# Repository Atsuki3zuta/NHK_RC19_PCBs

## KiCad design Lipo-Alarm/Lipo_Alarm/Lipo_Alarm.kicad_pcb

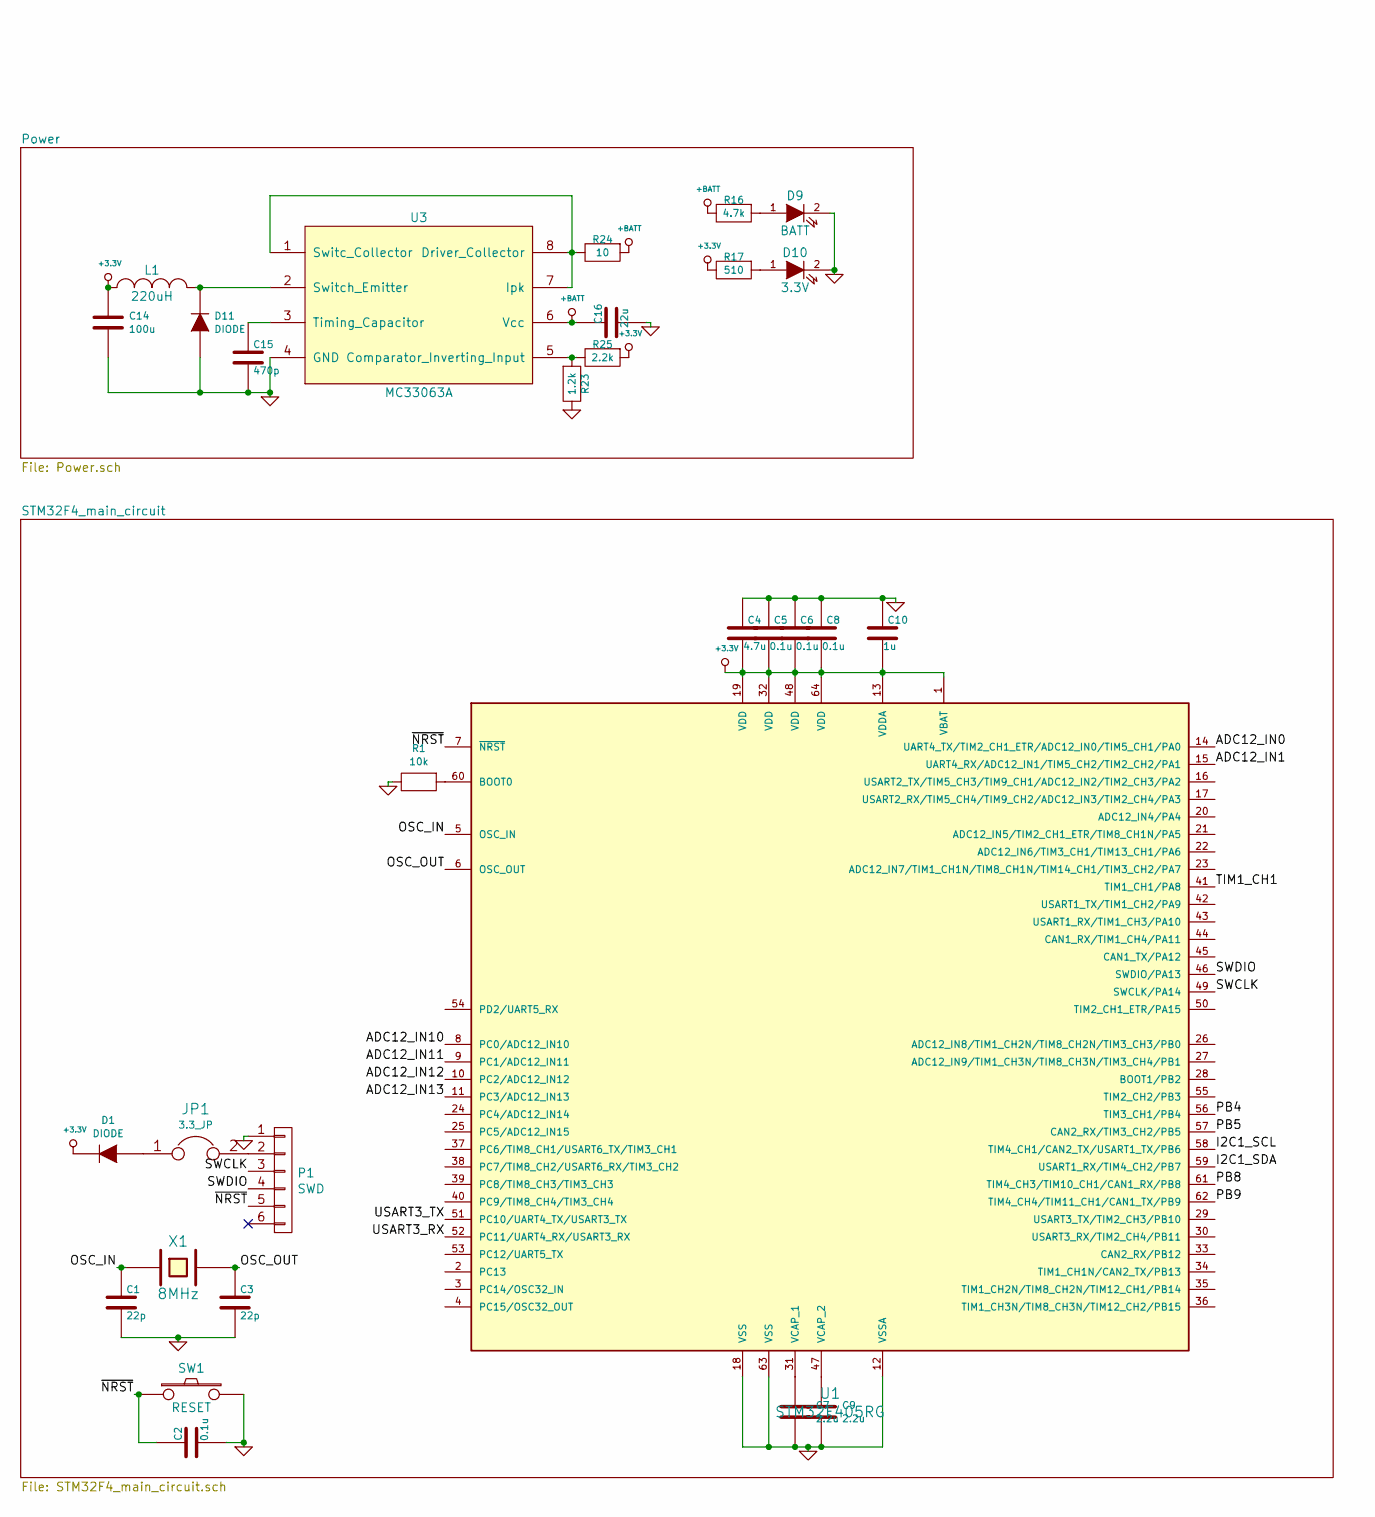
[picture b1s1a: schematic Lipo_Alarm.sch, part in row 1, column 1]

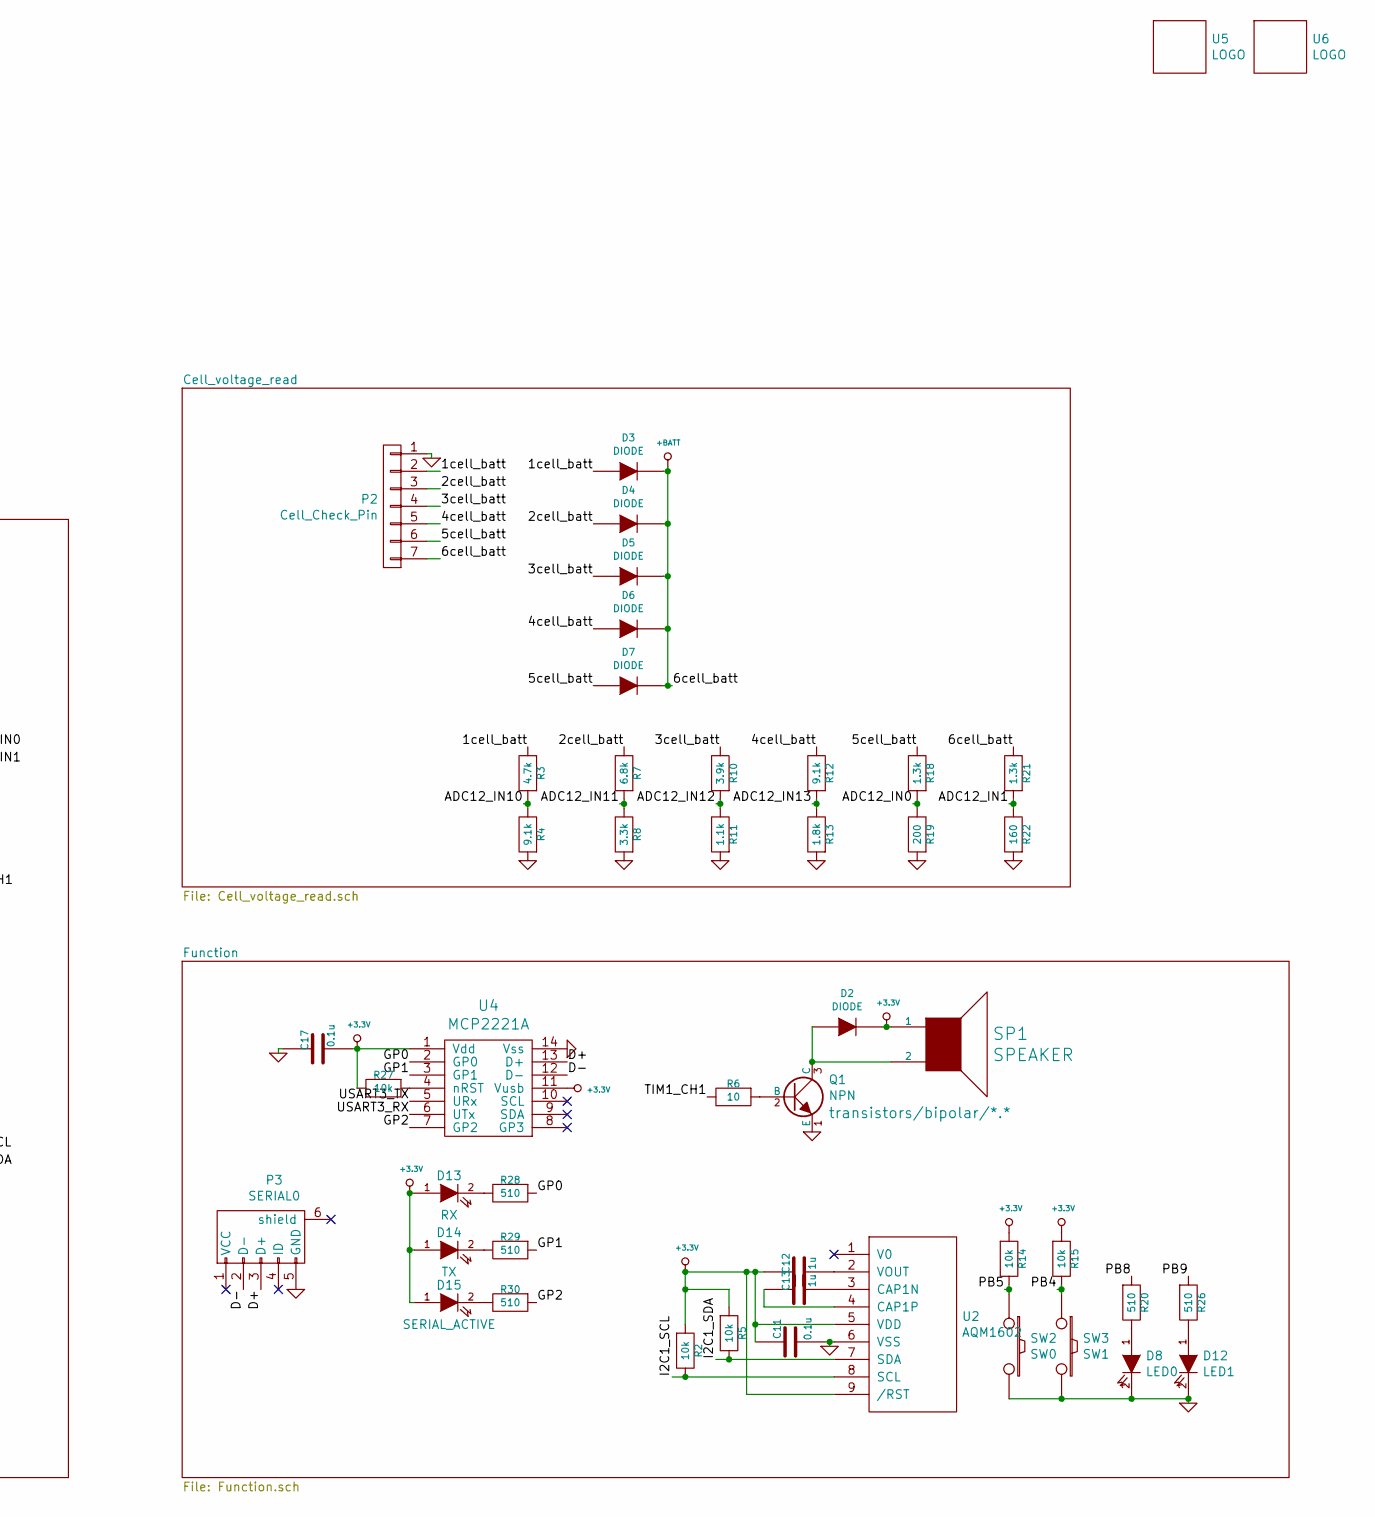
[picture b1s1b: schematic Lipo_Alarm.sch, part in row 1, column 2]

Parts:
C1, C3: 22p; C_0603
C2, C5, C6, C8, C11: 0.1u; C_0603
C4: 4.7u; C_0603
C7, C9: 2.2u; C_0603
C10, C12, C13: 1u; C_0603
C14: 100u; C_1206
C15: 470p; C_0603
C16: 22u; C_0805
C17: 0.1u; C_0805
D1, D2, D3, D4, D5, D6, D7, D11: DIODE; SOD-123
D8: LED0; LED_0603
D9: BATT; LED_0603
D10: 3.3V; LED_0603
D12: LED1; LED_0603
D13: RX; LED_0603
D14: TX; LED_0603
D15: SERIAL_ACTIVE; LED_0603
JP1: 3.3_JP; GS2
L1: 220uH; Inductor_Taiyo-Yuden_NR-60xx_HandSoldering
P1: SWD; ZH_6T
P2: Cell_Check_Pin; Pin_Header_Angled_1x07
P3: SERIAL0; USB_Micro-B_Molex_47346-0001
Q1: NPN; SOT-123
R1, R2, R5, R14, R15, R27: 10k; R_0603
R3, R16: 4.7k; R_0603
R4, R12: 9.1k; R_0603
R6, R24: 10; R_0603
R7: 6.8k; R_0603
R8: 3.3k; R_0603
R10: 3.9k; R_0603
R11: 1.1k; R_0603
R13: 1.8k; R_0603
R17, R20, R26, R28, R29, R30: 510; R_0603
R18, R21: 1.3k; R_0603
R19: 200; R_0603
R22: 160; R_0603
R23: 1.2k; R_0603
R25: 2.2k; R_0603
SP1: SPEAKER; UGCT7525AN4
SW1: RESET; SW_SPST_CK_RS282G05A3
SW2: SW0; SW_SPST_CK_RS282G05A3
SW3: SW1; SW_SPST_CK_RS282G05A3
U1: STM32F405RG; LQFP-64_10x10mm_Pitch0.5mm
U2: AQM1602
U3: MC33063A; SOIC-8_3.9x4.9mm_Pitch1.27mm
U4: MCP2221A; SOIC-14_3.9x8.7mm_Pitch1.27mm
U5: LOGO; Mini_Monster
U6: LOGO; Battery_logo_7.0x7.0
X1: 8MHz; Crystal_SMD_5032_2Pads

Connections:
+3.3V: C4.2, C5.2, C6.2, C8.2, C10.2, C11.2, C12.2, C14.1, C17.1, D1.1 (K), D2.1 (K), D13.1 (A), D14.1 (A), D15.1 (A), L1.1, R2.1, R5.1, R14.1, R15.1, R17.2, R25.1, R27.2, SP1.1, U1.1 (VBAT), U1.13 (VDDA), U1.19 (VDD), U1.32 (VDD), U1.48 (VDD), U1.64 (VDD), U2.5 (VDD), U2.9 (/RST), U4.1 (Vdd), U4.11 (Vusb)
+BATT: C16.2, D3.1 (K), D4.1 (K), D5.1 (K), D6.1 (K), D7.1 (K), P2.7, R16.2, R21.2, R24.1, U3.6 (Vcc)
/1cell_batt: D3.2 (A), P2.2, R3.2
/2cell_batt: D4.2 (A), P2.3, R7.2
/3cell_batt: D5.2 (A), P2.4, R10.2
/4cell_batt: D6.2 (A), P2.5, R12.2
/5cell_batt: D7.2 (A), P2.6, R18.2
/ADC12_IN0: R18.1, R19.2, U1.14 (UART4_TX/TIM2_CH1_ETR/ADC12_IN0/TIM5_CH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)
/ADC12_IN1: R21.1, R22.2, U1.15 (UART4_RX/ADC12_IN1/TIM5_CH2/TIM2_CH2/PA1)
/ADC12_IN10: R3.1, R4.2, U1.8 (PC0/ADC12_IN10)
/ADC12_IN11: R7.1, R8.2, U1.9 (PC1/ADC12_IN11)
/ADC12_IN12: R10.1, R11.2, U1.10 (PC2/ADC12_IN12)
/ADC12_IN13: R12.1, R13.2, U1.11 (PC3/ADC12_IN13)
/D+: P3.3 (D+), U4.13 (D+)
/D-: P3.2 (D-), U4.12 (D-)
/GP0: R28.1, U4.2 (GP0)
/GP1: R29.1, U4.3 (GP1)
/GP2: R30.1, U4.7 (GP2)
/I2C1_SCL: R2.2, U1.58 (TIM4_CH1/CAN2_TX/USART1_TX/PB6), U2.8 (SCL)
/I2C1_SDA: R5.2, U1.59 (USART1_RX/TIM4_CH2/PB7), U2.7 (SDA)
/OSC_IN: C1.1, U1.5 (OSC_IN), X1.1
/OSC_OUT: C3.1, U1.6 (OSC_OUT), X1.2
/PB4: R15.2, SW3.1, U1.56 (TIM3_CH1/PB4)
/PB5: R14.2, SW2.1, U1.57 (CAN2_RX/TIM3_CH2/PB5)
/PB8: R20.1, U1.61 (TIM4_CH3/TIM10_CH1/CAN1_RX/PB8)
/PB9: R26.1, U1.62 (TIM4_CH4/TIM11_CH1/CAN1_TX/PB9)
/SWCLK: P1.3, U1.49 (SWCLK/PA14)
/SWDIO: P1.4, U1.46 (SWDIO/PA13)
/TIM1_CH1: R6.2, U1.41 (TIM1_CH1/PA8)
/USART3_RX: U1.52 (PC11/UART4_RX/USART3_RX), U4.6 (UTx)
/USART3_TX: U1.51 (PC10/UART4_TX/USART3_TX), U4.5 (URx)
/~NRST: C2.2, P1.5, SW1.1, U1.7 (~NRST)
GND: C1.2, C2.1, C3.2, C4.1, C5.1, C6.1, C7.2, C8.1, C9.2, C10.1, C11.1, C14.2, C15.1, C16.1, C17.2, D8.2 (K), D9.2 (K), D10.2 (K), D11.2 (A), D12.2 (K), P1.1, P2.1, P3.5 (GND), Q1.1 (E), R1.2, R4.1, R8.1, R11.1, R13.1, R19.1, R22.1, R23.2, SW1.2, SW2.2, SW3.2, U1.12 (VSSA), U1.18 (VSS), U1.63 (VSS), U2.6 (VSS), U3.4 (GND), U4.14 (Vss)
unnamed: C7.1, U1.31 (VCAP_1)
unnamed: C9.1, U1.47 (VCAP_2)
unnamed: C12.1, U2.2 (VOUT)
unnamed: C13.1, U2.3 (CAP1N)
unnamed: C13.2, U2.4 (CAP1P)
unnamed: C15.2, U3.3 (Timing_Capacitor)
unnamed: D1.2 (A), JP1.1
unnamed: D2.2 (A), Q1.3 (C), SP1.2
unnamed: D8.1 (A), R20.2
unnamed: D9.1 (A), R16.1
unnamed: D10.1 (A), R17.1
unnamed: D11.1 (K), L1.2, U3.2 (Switch_Emitter)
unnamed: D12.1 (A), R26.2
unnamed: D13.2 (K), R28.2
unnamed: D14.2 (K), R29.2
unnamed: D15.2 (K), R30.2
unnamed: JP1.2, P1.2
unnamed: Q1.2 (B), R6.1
unnamed: R1.1, U1.60 (BOOT0)
unnamed: R23.1, R25.2, U3.5 (Comparator_Inverting_Input)
unnamed: R24.2, U3.1 (Switc_Collector), U3.7 (Ipk), U3.8 (Driver_Collector)
unnamed: R27.1, U4.4 (nRST)

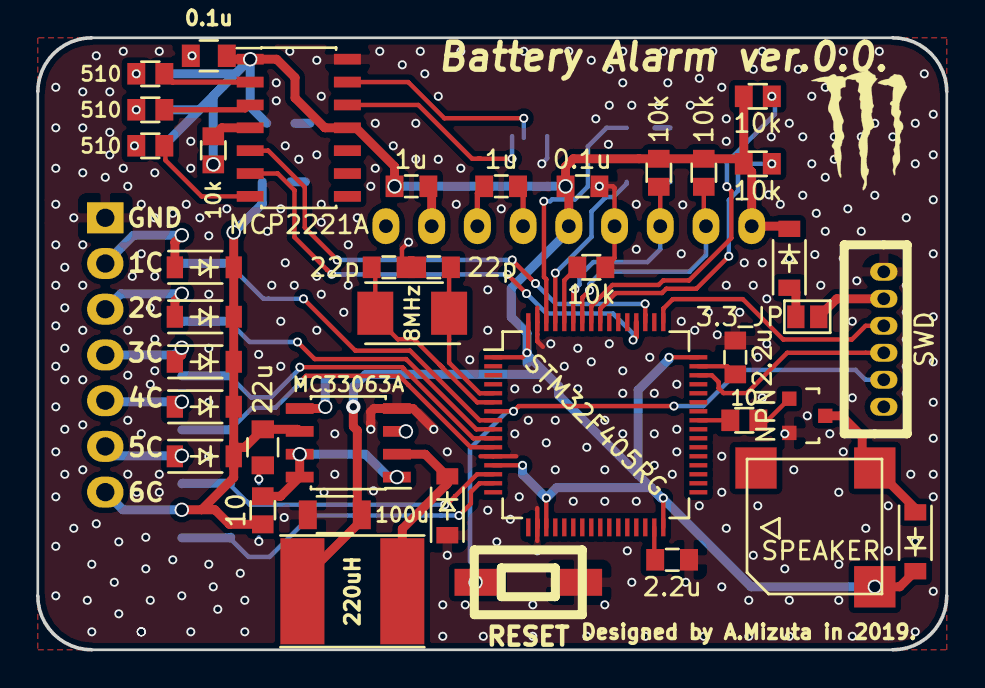
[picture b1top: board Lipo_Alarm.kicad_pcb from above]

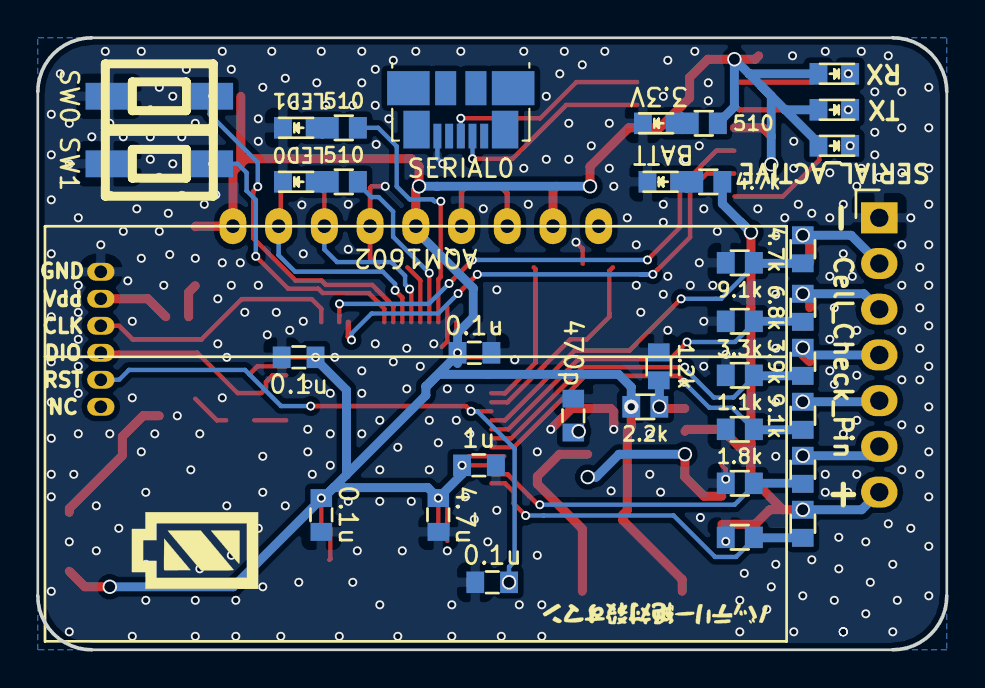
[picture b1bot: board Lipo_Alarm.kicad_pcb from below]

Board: 2 copper layers, 50.5 x 34.0 mm, 78 parts (38 on the bottom side), 55 nets.

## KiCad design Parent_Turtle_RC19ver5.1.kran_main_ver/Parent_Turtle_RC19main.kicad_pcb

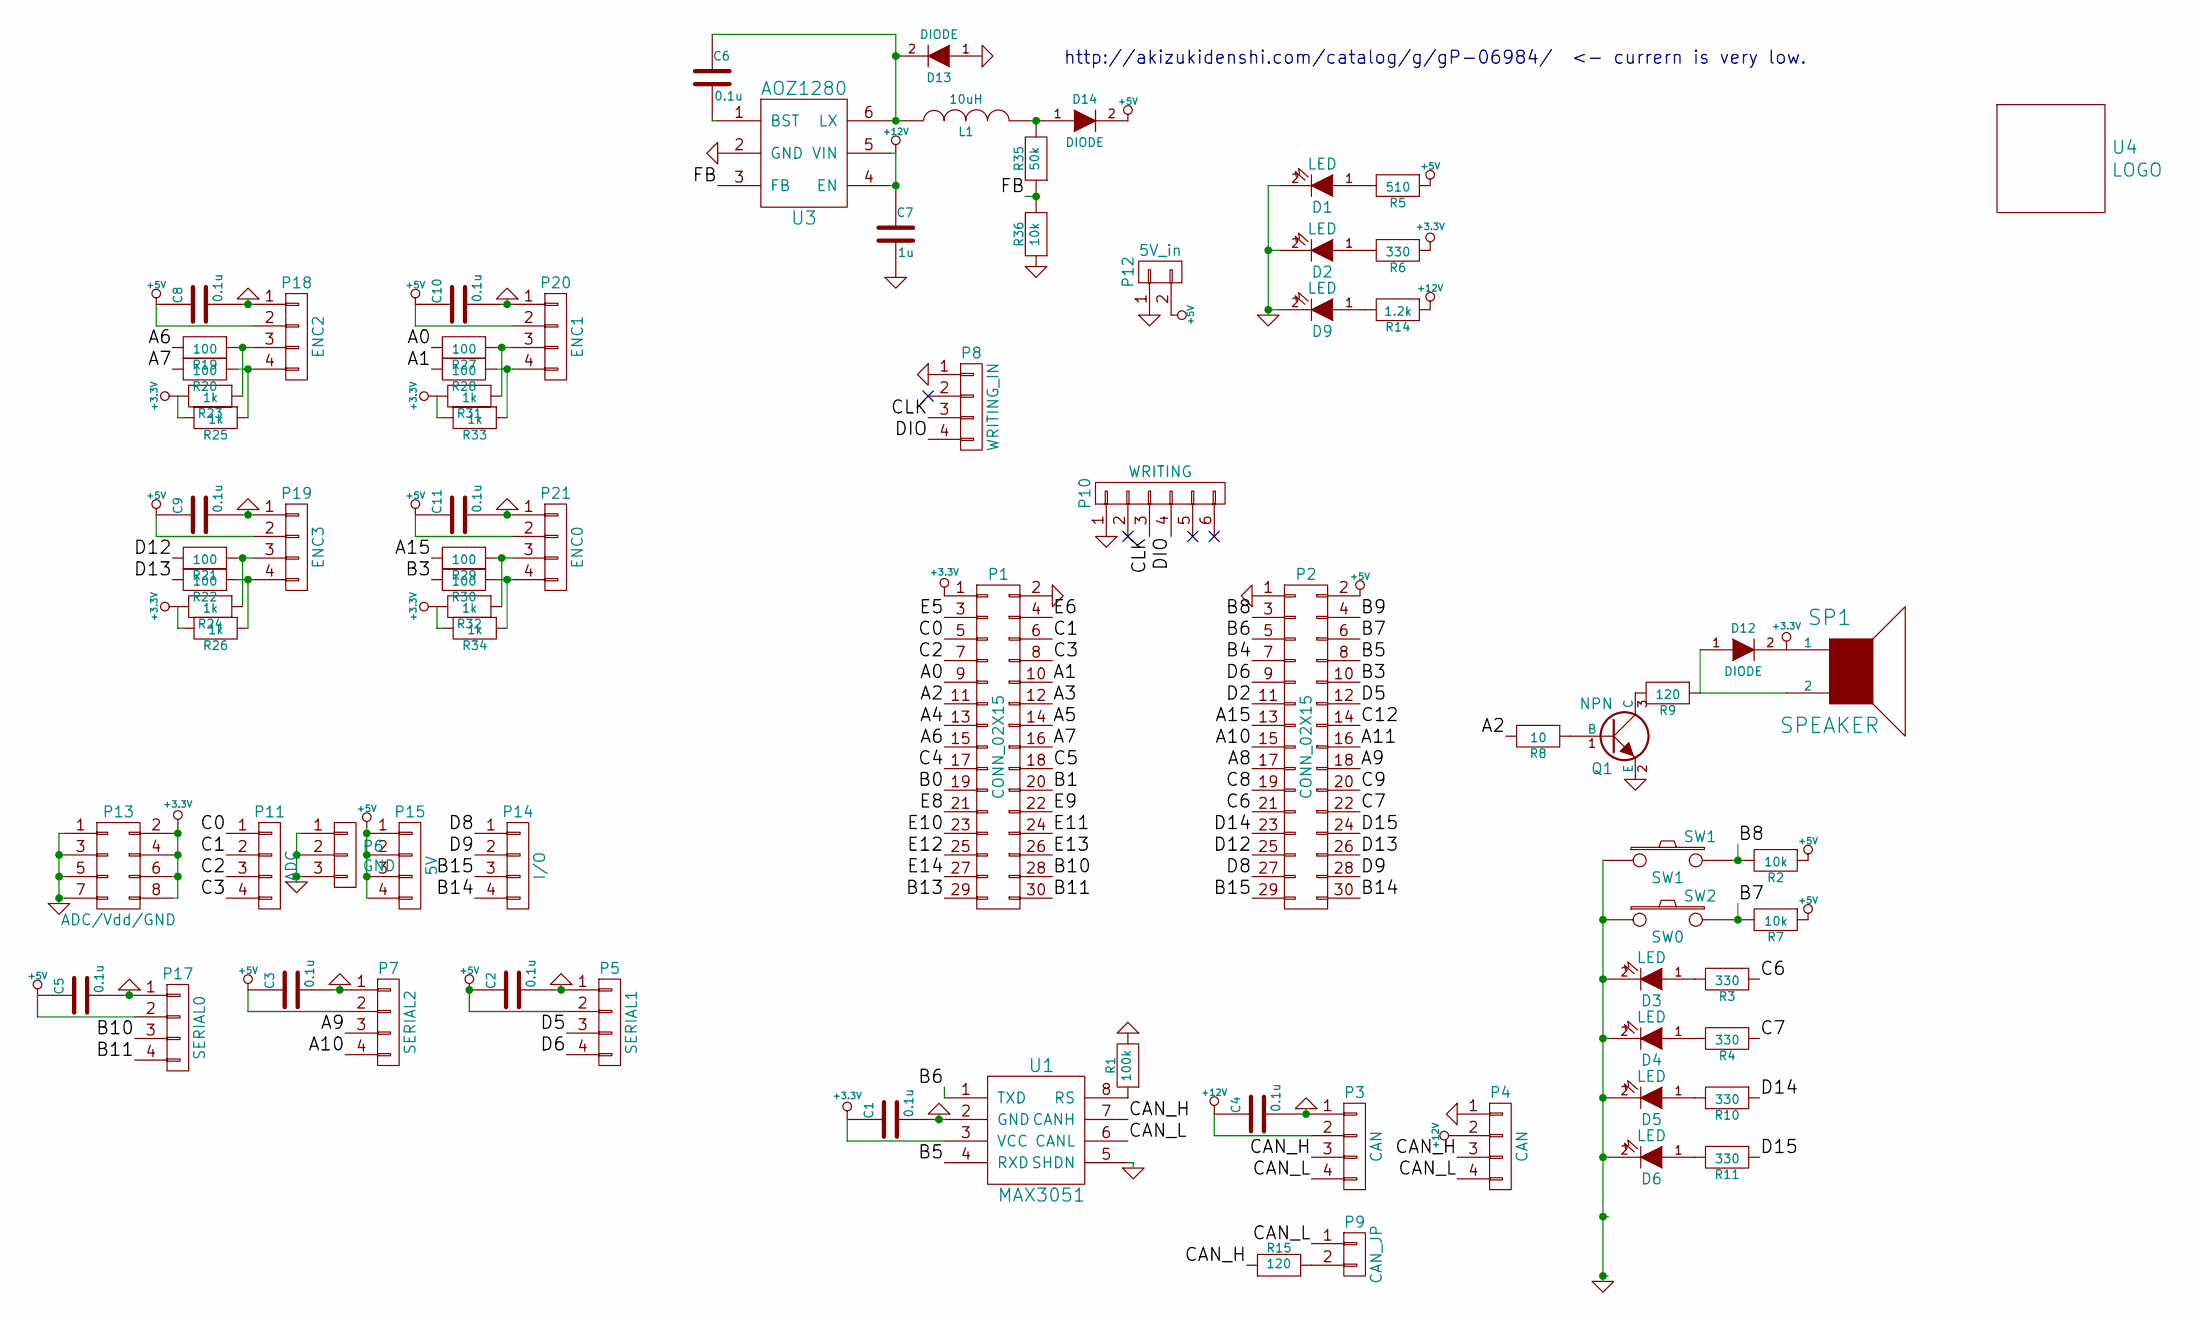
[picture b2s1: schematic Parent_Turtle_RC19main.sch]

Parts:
C1, C2, C3, C4, C5, C6, C8, C9, C10, C11: 0.1u; C_0603
C7: 1u; C_0603
D1, D2, D3, D4, D5, D6, D9: LED; LED-3MM
D12, D13, D14: DIODE; SOD-123
L1: 10uH; Inductor_Taiyo-Yuden_NR-50xx_HandSoldering
P1, P2: CONN_02X15; Socket_Strip_Straight_2x15
P3: CAN; XA_4T
P4: CAN; XA_4LC
P5: SERIAL1; XA_4T
P6: GND; PinHeader_1x03_P2.54mm_Vertical
P7: SERIAL2; XA_4T
P8: WRITING_IN; XA_4LC
P9: CAN_JP; Pin_Header_Straight_1x02
P10: WRITING; Socket_Strip_Straight_1x06
P11: ADC; Pin_Header_Straight_1x04
P12: 5V_in; XA_2T
P13: ADC/Vdd/GND; Pin_Header_Straight_2x04
P14: I/O; Pin_Header_Straight_1x04
P15: 5V; PinHeader_1x04_P2.54mm_Vertical
P17: SERIAL0; XA_4T
P18: ENC2; XA_4T
P19: ENC3; XA_4T
P20: ENC1; XA_4T
P21: ENC0; XA_4T
Q1: NPN; SOT-23
R1: 100k; R_0603
R2, R7, R36: 10k; R_0603
R3, R4, R6, R10, R11: 330; R_0603
R5: 510; R_0603
R8: 10; R_0603
R9, R15: 120; R_0603
R14: 1.2k; R_0603
R19, R20, R21, R22, R27, R28, R29, R30: 100; R_0603
R23, R24, R25, R26, R31, R32, R33, R34: 1k; R_0603
R35: 50k; R_0603
SP1: SPEAKER; UGCT7525AN4
SW1: SW1; RP_TroughHole_Button
SW2: SW0; RP_TroughHole_Button
U1: MAX3051; SOIC-8_3.9x4.9mm_Pitch1.27mm
U3: AOZ1280; TSOT-6-MK06A
U4: LOGO; Turtle_Logo_15.0x15.0

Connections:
+3.3V: C1.1, D12.2 (K), P1.1, P13.2, P13.4, P13.6, P13.8, R6.1, R23.2, R24.2, R25.2, R26.2, R31.2, R32.2, R33.2, R34.2, SP1.1, U1.3 (VCC)
+5V: C2.1, C3.1, C5.1, C8.1, C9.1, C10.1, C11.1, D14.2 (K), P2.2, P5.2, P7.2, P12.2, P15.1, P15.2, P15.3, P15.4, P17.2, P18.2, P19.2, P20.2, P21.2, R2.1, R5.1, R7.1
+12V: C4.1, C7.1, P3.2, P4.2, R14.1, U3.4 (EN), U3.5 (VIN)
/A0: P1.9, R27.2
/A1: P1.10, R28.2
/A2: P1.11, R8.2
/A3: P1.12
/A4: P1.13
/A5: P1.14
/A6: P1.15, R19.2
/A7: P1.16, R20.2
/A8: P2.17
/A9: P2.18, P7.3
/A10: P2.15, P7.4
/A11: P2.16
/A15: P2.13, R29.2
/B0: P1.19
/B1: P1.20
/B3: P2.10, R30.2
/B4: P2.7
/B5: P2.8, U1.4 (RXD)
/B6: P2.5, U1.1 (TXD)
/B7: P2.6, R7.2, SW2.2
/B8: P2.3, R2.2, SW1.2
/B9: P2.4
/B10: P1.28, P17.3
/B11: P1.30, P17.4
/B13: P1.29
/B14: P2.30, P14.4
/B15: P2.29, P14.3
/C0: P1.5, P11.1
/C1: P1.6, P11.2
/C2: P1.7, P11.3
/C3: P1.8, P11.4
/C4: P1.17
/C5: P1.18
/C6: P2.21, R3.1
/C7: P2.22, R4.1
/C8: P2.19
/C9: P2.20
/C12: P2.14
/CAN_H: P3.3, P4.3, R15.1, U1.7 (CANH)
/CAN_L: P3.4, P4.4, P9.1, U1.6 (CANL)
/CLK: P8.3, P10.3
/D2: P2.11
/D5: P2.12, P5.3
/D6: P2.9, P5.4
/D8: P2.27, P14.1
/D9: P2.28, P14.2
/D12: P2.25, R21.2
/D13: P2.26, R22.2
/D14: P2.23, R10.1
/D15: P2.24, R11.1
/DIO: P8.4, P10.4
/E5: P1.3
/E6: P1.4
/E8: P1.21
/E9: P1.22
/E10: P1.23
/E11: P1.24
/E12: P1.25
/E13: P1.26
/E14: P1.27
/FB: R35.1, R36.2, U3.3 (FB)
GND: C1.2, C2.2, C3.2, C4.2, C5.2, C7.2, C8.2, C9.2, C10.2, C11.2, D1.2 (K), D2.2 (K), D3.2 (K), D4.2 (K), D5.2 (K), D6.2 (K), D9.2 (K), D13.1 (A), P1.2, P2.1, P3.1, P4.1, P5.1, P6.1, P6.2, P6.3, P7.1, P8.1, P10.1, P12.1, P13.1, P13.3, P13.5, P13.7, P17.1, P18.1, P19.1, P20.1, P21.1, Q1.2 (E), R1.2, R36.1, SW1.1, SW2.1, U1.2 (GND), U1.5 (SHDN), U3.2 (GND)
unnamed: C6.1, D13.2 (K), L1.1, U3.6 (LX)
unnamed: C6.2, U3.1 (BST)
unnamed: D1.1 (A), R5.2
unnamed: D2.1 (A), R6.2
unnamed: D3.1 (A), R3.2
unnamed: D4.1 (A), R4.2
unnamed: D5.1 (A), R10.2
unnamed: D6.1 (A), R11.2
unnamed: D9.1 (A), R14.2
unnamed: D12.1 (A), R9.1, SP1.2
unnamed: D14.1 (A), L1.2, R35.2
unnamed: P9.2, R15.2
unnamed: P18.3, R19.1, R23.1
unnamed: P18.4, R20.1, R25.1
unnamed: P19.3, R21.1, R24.1
unnamed: P19.4, R22.1, R26.1
unnamed: P20.3, R27.1, R31.1
unnamed: P20.4, R28.1, R33.1
unnamed: P21.3, R29.1, R32.1
unnamed: P21.4, R30.1, R34.1
unnamed: Q1.1 (B), R8.1
unnamed: Q1.3 (C), R9.2
unnamed: R1.1, U1.8 (RS)

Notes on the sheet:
http://akizukidenshi.com/catalog/g/gP-06984/
<- currern is very low.

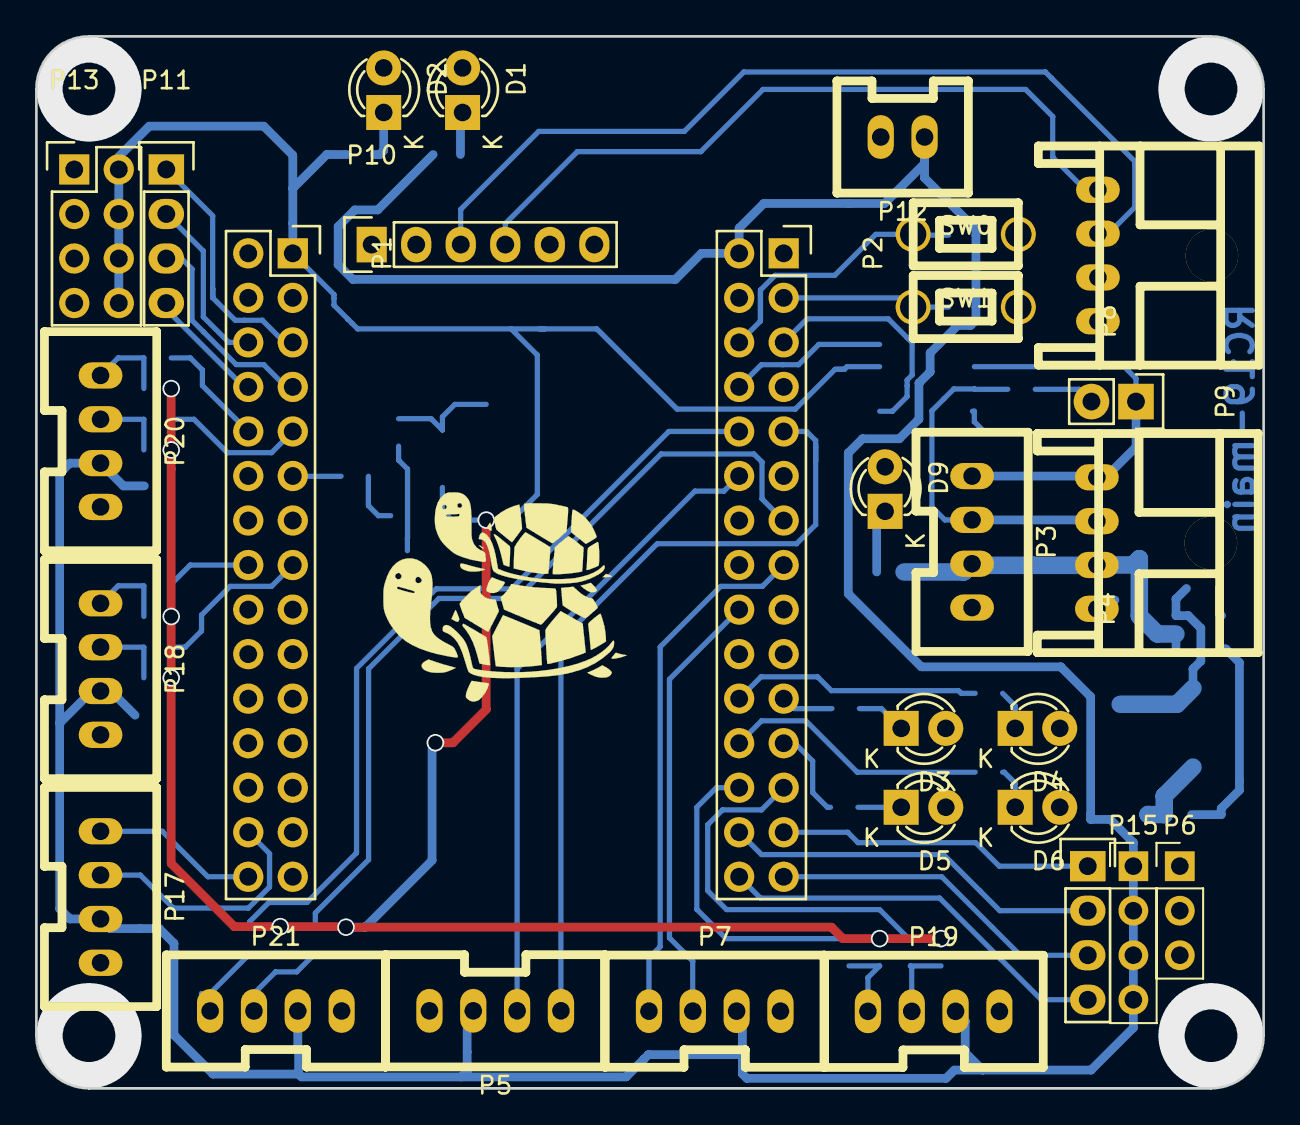
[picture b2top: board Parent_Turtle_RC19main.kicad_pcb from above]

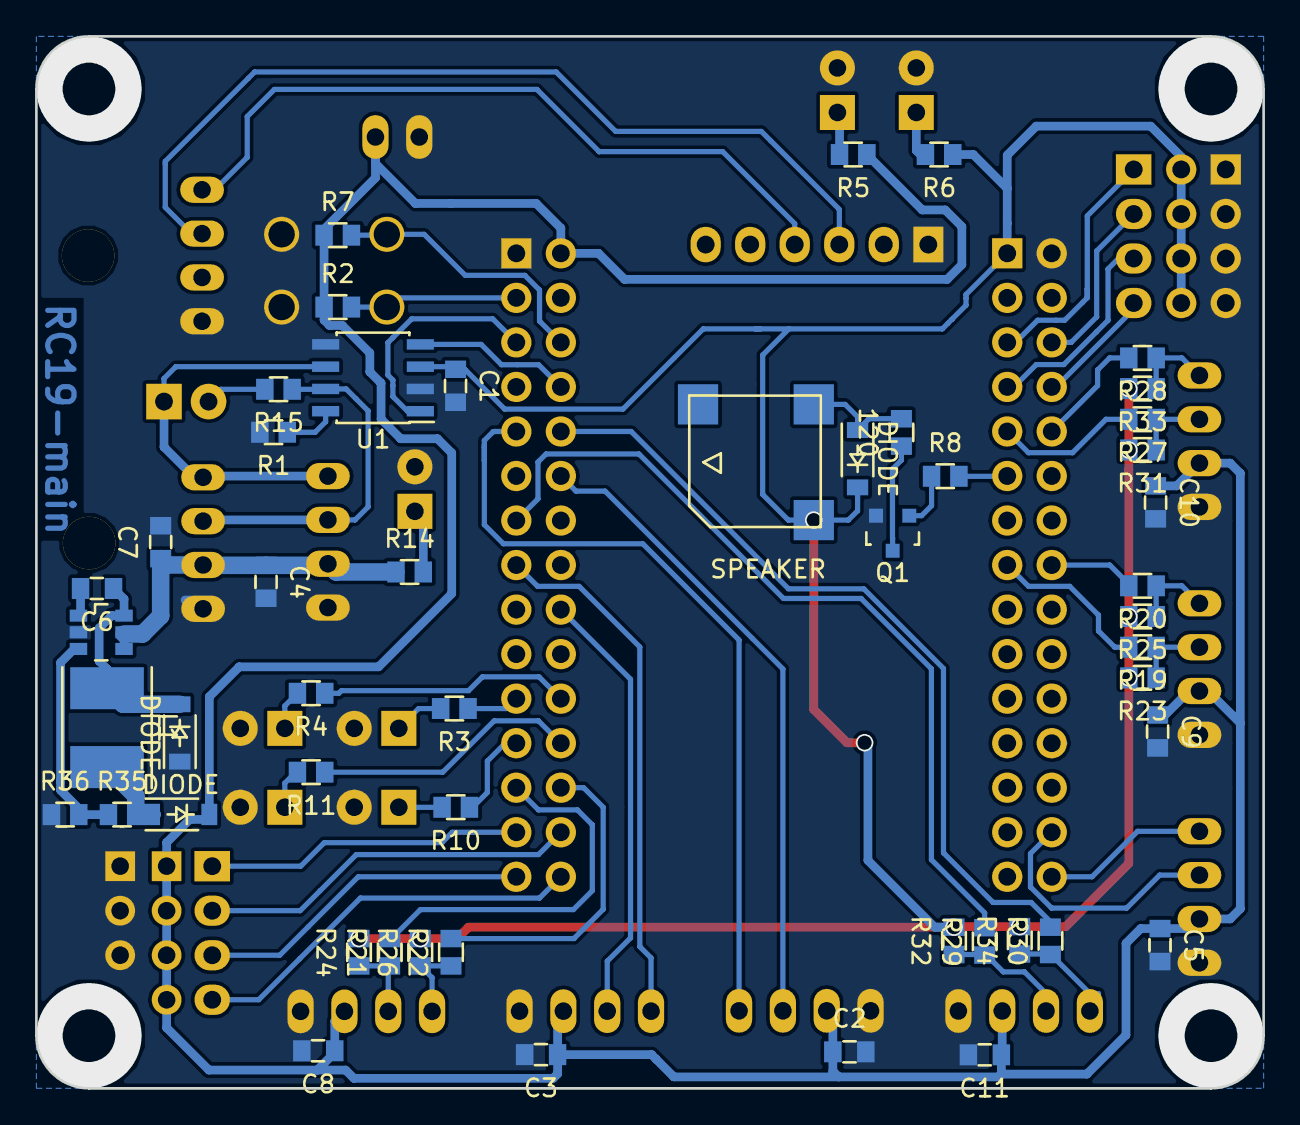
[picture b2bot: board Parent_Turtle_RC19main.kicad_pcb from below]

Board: 2 copper layers, 70.0 x 60.0 mm, 80 parts (50 on the bottom side), 63 nets.

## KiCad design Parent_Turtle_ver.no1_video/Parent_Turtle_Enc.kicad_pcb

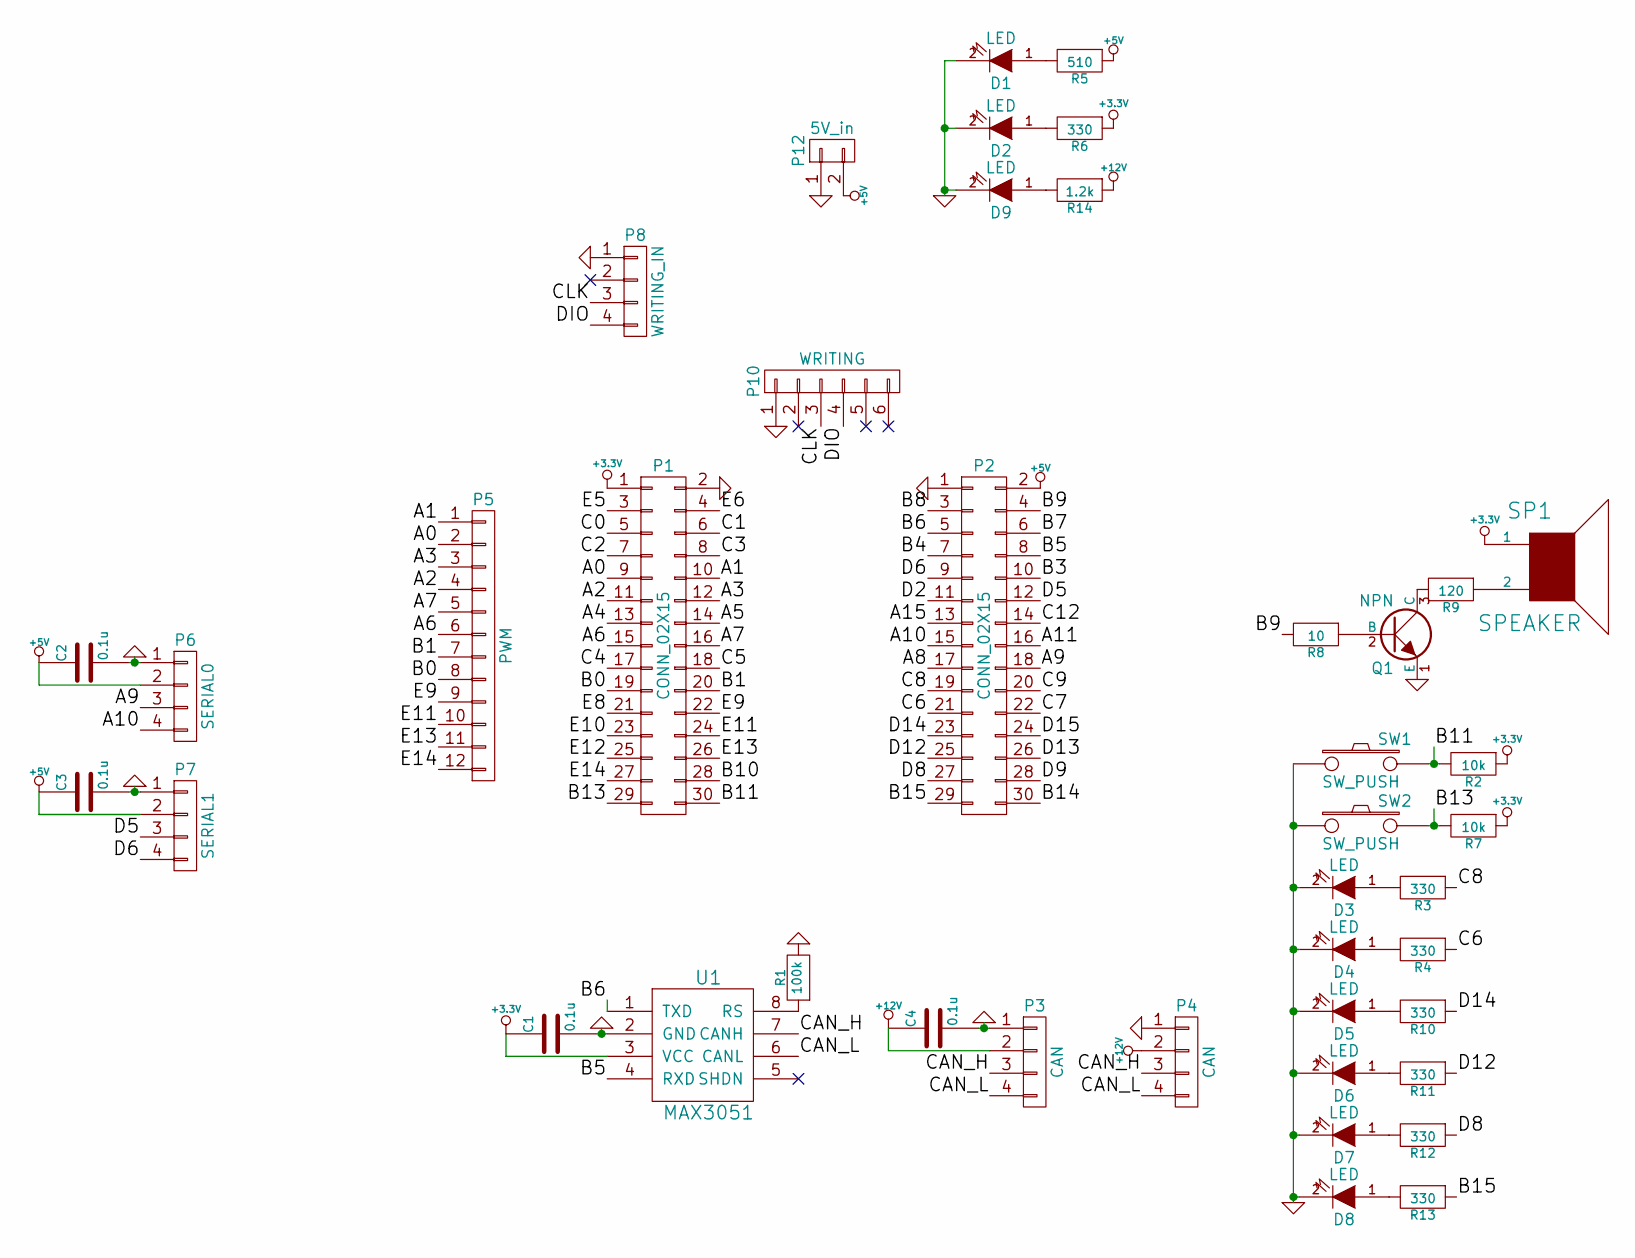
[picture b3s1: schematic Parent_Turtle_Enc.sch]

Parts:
C1, C2, C3, C4: 0.1u; C_0603
D1, D2, D3, D4, D5, D6, D7, D8, D9: LED; LED-3MM
P1, P2: CONN_02X15; Socket_Strip_Straight_2x15
P3: CAN; XA_4T
P4: CAN; XA_4LC
P5: PWM; Pin_Header_Straight_1x12
P6: SERIAL0; XA_4T
P7: SERIAL1; XA_4T
P8: WRITING_IN; XA_4LC
P10: WRITING; Socket_Strip_Straight_1x06
P12: 5V_in; XA_2T
Q1: NPN; SOT-23
R1: 100k; R_0603
R2, R7: 10k; R_0603
R3, R4, R6, R10, R11, R12, R13: 330; R_0603
R5: 510; R_0603
R8: 10; R_0603
R9: 120; R_0603
R14: 1.2k; R_0603
SP1: SPEAKER; UGCT7525AN4
SW1, SW2: SW_PUSH; SW_PUSH_6mm
U1: MAX3051; SOIC-8_3.9x4.9mm_Pitch1.27mm

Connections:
+3.3V: C1.1, P1.1, R2.1, R6.1, R7.1, SP1.1, U1.3 (VCC)
+5V: C2.1, C3.1, P2.2, P6.2, P7.2, P12.2, R5.1
+12V: C4.1, P3.2, P4.2, R14.1
/A0: P1.9, P5.2
/A1: P1.10, P5.1
/A2: P1.11, P5.4
/A3: P1.12, P5.3
/A4: P1.13
/A5: P1.14
/A6: P1.15, P5.6
/A7: P1.16, P5.5
/A8: P2.17
/A9: P2.18, P6.3
/A10: P2.15, P6.4
/A11: P2.16
/A15: P2.13
/B0: P1.19, P5.8
/B1: P1.20, P5.7
/B3: P2.10
/B4: P2.7
/B5: P2.8, U1.4 (RXD)
/B6: P2.5, U1.1 (TXD)
/B7: P2.6
/B8: P2.3
/B9: P2.4, R8.2
/B10: P1.28
/B11: P1.30, R2.2, SW1.2
/B13: P1.29, R7.2, SW2.2
/B14: P2.30
/B15: P2.29, R13.1
/C0: P1.5
/C1: P1.6
/C2: P1.7
/C3: P1.8
/C4: P1.17
/C5: P1.18
/C6: P2.21, R4.1
/C7: P2.22
/C8: P2.19, R3.1
/C9: P2.20
/C12: P2.14
/CAN_H: P3.3, P4.3, U1.7 (CANH)
/CAN_L: P3.4, P4.4, U1.6 (CANL)
/CLK: P8.3, P10.3
/D2: P2.11
/D5: P2.12, P7.3
/D6: P2.9, P7.4
/D8: P2.27, R12.1
/D9: P2.28
/D12: P2.25, R11.1
/D13: P2.26
/D14: P2.23, R10.1
/D15: P2.24
/DIO: P8.4, P10.4
/E5: P1.3
/E6: P1.4
/E8: P1.21
/E9: P1.22, P5.9
/E10: P1.23
/E11: P1.24, P5.10
/E12: P1.25
/E13: P1.26, P5.11
/E14: P1.27, P5.12
GND: C1.2, C2.2, C3.2, C4.2, D1.2 (K), D2.2 (K), D3.2 (K), D4.2 (K), D5.2 (K), D6.2 (K), D7.2 (K), D8.2 (K), D9.2 (K), P1.2, P2.1, P3.1, P4.1, P6.1, P7.1, P8.1, P10.1, P12.1, Q1.1 (E), R1.2, SW1.1, SW2.1, U1.2 (GND)
unnamed: D1.1 (A), R5.2
unnamed: D2.1 (A), R6.2
unnamed: D3.1 (A), R3.2
unnamed: D4.1 (A), R4.2
unnamed: D5.1 (A), R10.2
unnamed: D6.1 (A), R11.2
unnamed: D7.1 (A), R12.2
unnamed: D8.1 (A), R13.2
unnamed: D9.1 (A), R14.2
unnamed: Q1.2 (B), R8.1
unnamed: Q1.3 (C), R9.2
unnamed: R1.1, U1.8 (RS)
unnamed: R9.1, SP1.2

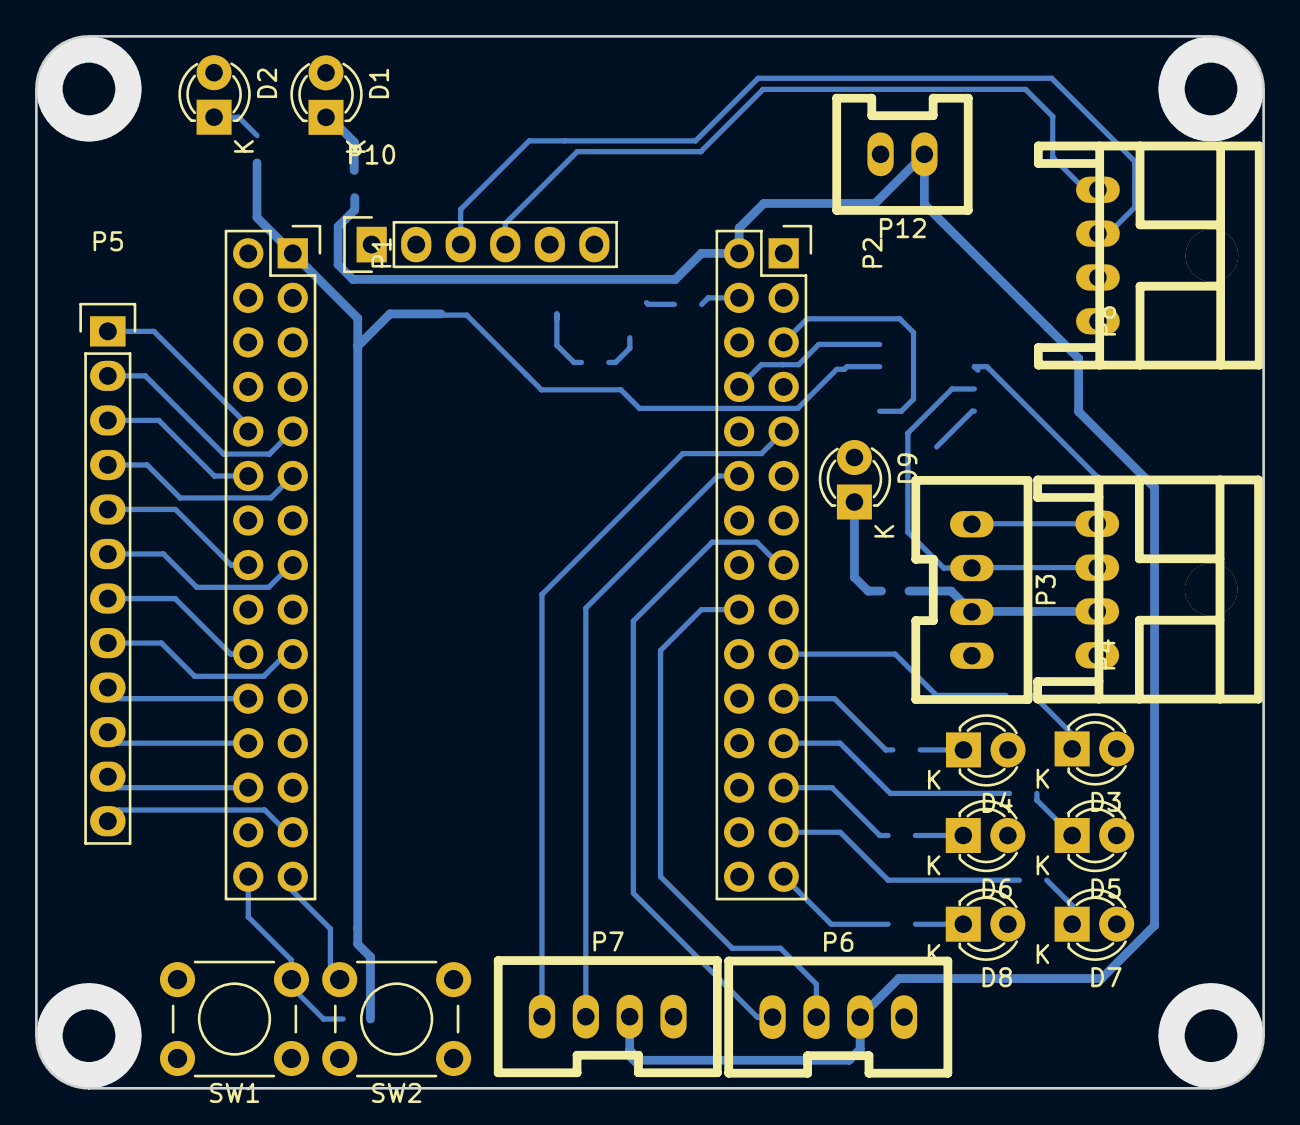
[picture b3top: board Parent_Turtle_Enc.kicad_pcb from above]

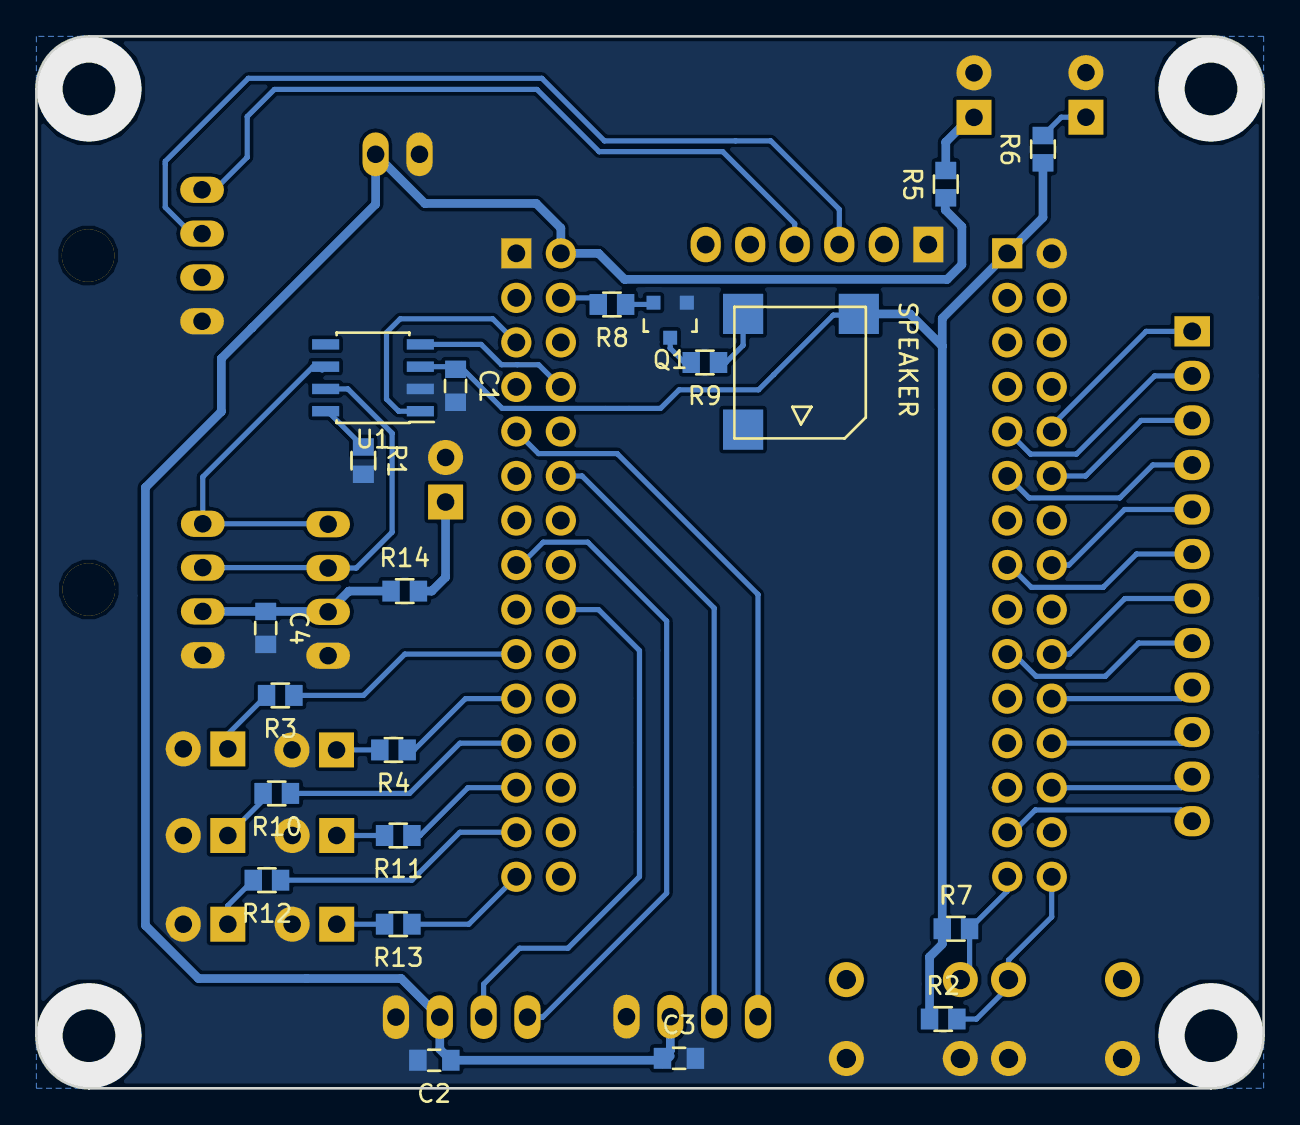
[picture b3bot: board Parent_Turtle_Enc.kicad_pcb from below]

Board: 2 copper layers, 70.0 x 60.0 mm, 42 parts (21 on the bottom side), 48 nets.
